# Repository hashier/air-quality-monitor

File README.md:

# air-quality-monitor

DIY air quality monitor on an ESP32-C6, running ESPHome and reporting to Home Assistant.

## Hardware

- **ESP32-C6** dev board (`esp32-c6-devkitc-1`)
- **Sensirion SCD40**: CO2, temperature, humidity (I2C `0x62`)
- **Sensirion SPS30**: particulate matter PM1.0 / 2.5 / 4.0 / 10.0 (I2C `0x69`, 5V)
- **SSD1306** 128x64 OLED (I2C `0x3C`)
- **WS2812** RGB LED (GPIO8)
- **ENS160 + AHT21** combo module: TVOC plus derived eCO2/AQI, AHT21
  temperature/humidity for compensation (I2C `0x52` / `0x38`). Under
  evaluation on the breadboard; mainly calculated values instead of measured
  ones, so it probably won't make the final PCB.

All devices share one I2C bus at 100 kHz (the SPS30 datasheet ceiling).

## Repo layout

- `esphome/`: firmware (ESPHome config + secrets template)
- `kicad/`: custom PCB (planned)
- `case/`: 3D-printed enclosure (planned)

## Firmware

```fish
cd esphome
cp secrets.yaml.example secrets.yaml   # then fill in real values
esphome run air-quality-monitor.yaml
```

`secrets.yaml` holds WiFi / API / OTA credentials and is gitignored. Never commit it.

## Notes

- **SCD40 auto-recovery:** the sensor can get knocked out of periodic measurement (a flaky power connection resets it). A YAML watchdog detects CO2 going stale and re-inits it over raw I2C (stop, then start). Two Home Assistant diagnostics track this: `CO2 Stall Count` and `CO2 Currently Stalled`.
- **Temperature offset** (`6.5C`) is a provisional self-heating correction for the breadboard build. Re-tune in the final enclosure by comparing side by side against a reference.
- **Warm-up filters** drop the SCD40 startup transient (temperature/humidity 5 min, CO2 30 s).

## Status

Work in progress: currently on a breadboard. Custom PCB and enclosure are next.

## To test

- **Separate 3.3V regulator for the SCD40:** power it from 5V through its own LDO (AP2112K-3.3, 1 µF on input and output, EN tied to VIN) instead of the ESP32 board's 3V3 pin. Sensirion's SCD4x datasheet recommends a separate LDO and allows at most 30 mV supply ripple, and the SCD40 peaks at 205 mA while the ESP32's WiFi bursts share the same regulator. Compare `CO2 Stall Count` before and after.
- **Everything on one I2C bus:** SCD40, OLED and SPS30 together, with the SPS30 on a cable as long as the case needs. Each breakout brings its own pull-ups, so check whether the bus still works with all of them in parallel, and whether the SPS30 needs extra ones.

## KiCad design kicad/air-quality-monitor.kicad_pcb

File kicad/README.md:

# kicad

Custom PCB design (KiCad) for the air quality monitor. Planned.

Target layout: thermal zoning so the SCD40 sits away from the ESP32 and
regulator heat and the SPS30 exhaust, on a slot-isolated peninsula, with the
SPS30 airflow ducted to separate case vents. See the project notes for details.

## v1 design (draft, untested)

**Untested.** Nothing below has been built yet. Parts of it depend on the
breadboard tests in the main README's "To test" section, and change if a test
says so.

One PCB for every build, ordered in a batch of 5 and hand-soldered (through-hole
where possible, no assembly service). Each build gets its own 3D-printed case:

| Build | SCD40 | OLED | SPS30 |
|---|---|---|---|
| Living room | yes | yes | yes |
| Bedroom | yes | no | no |
| Portable (power bank, car) | yes | yes | no |

Home Assistant is the control plane, so there are no buttons or buzzers. Unused
dev board pins keep their holes for wiring something on later. Battery power is
for a later version.

### Power

- **Input:** a USB-C breakout board (AliExpress 1005004848153846, 20.2 x 14 mm)
  on an 8-pin 2.54 mm header, 5V, no USB PD. Only VBUS and GND are wired. The
  board has its own 5.1 kΩ resistors on CC1 and CC2, so a USB-C charger turns
  on 5V. Pin order and screw holes still need checking on the real board.
- **5V rail** feeds the SPS30 and both 3.3V regulators directly.
- **Dev board 5V pin** (J1 pin 14) is fed from the 5V rail through a Schottky
  diode, which a jumper cap bypasses by default (see below). With the cap
  pulled, plugging in the dev board's own USB at the same time can't push
  current back into the PCB's USB-C. In Espressif's DevKitC-1 schematic v1.4,
  each USB port reaches `VCC_5V` through a 1N5819, and `VCC_5V` is the 5V pin
  with no diode in between.
- **Two AP2112K-3.3** (SOT-23-5) from the 5V rail, each with EN tied to VIN and
  1 µF on input and output, instead of the dev board's 3V3, which also feeds the
  WiFi:
  - **3V3_SCD** feeds only the SCD40. Pending the LDO test.
  - **3V3_AUX** feeds the OLED and the two JST ZH sensor sockets.
- **Fallback to the dev board's rails:**
  - each 3.3V rail can be switched to the dev board's 3V3 pin with a 3-pad
    solder jumper (`SolderJumper_3_Bridged12`): a thin trace joins the LDO side
    from the factory, so the board works without soldering a jumper; to switch,
    cut it and put a solder blob on the dev board side. Solder jumpers,
    not pin headers with caps, because a push-fit contact in the SCD40's supply
    is the kind of fault behind the earlier stalls;
  - a 2-pin header with a jumper cap (`Jumper_2_Bridged`) across the Schottky
    diode, cap on by default: the dev board gets the full 5V, not 5V minus the
    diode drop, likely too little for its AMS1117 (an ESP32-S3 board went into
    a brownout loop at 4.9V on its 5V pin). A loose cap only puts the diode back
    in the path. Pull the cap before plugging in both USB cables, otherwise the
    device on the PCB's USB-C gets fed backwards. With the cap on, the dev board's
    own USB also powers the whole PCB;
  - two optional electrolytics (C6 100µF, C7 470µF, not fitted) on the dev
    board's 3V3 pin: that pair (570µF) stopped the same S3 board's brownout loop
    at 5.0V.

### Dev board

ESP32-C6-DevKitC-1 or a pin-compatible copy, soldered through its pin headers:
2 rows of 16 pins at 2.54 mm, rows 22.86 mm apart, board 25.4 × 51.8 mm
(Espressif dimension drawing v1.2). Pin 16 on both rows stays unconnected:
it is NC on Espressif's board and GND on the QSZNTEC copy.

Every header hole the PCB connects to (5V, 3V3, SDA, SCL, and GND on two pins
with one jumper each) goes through a cuttable solder jumper
(`SolderJumper_2_Bridged` in KiCad's `Jumper` library), so another board's pin
in that position is never shorted to anything. A board with a
different pinout fits by cutting the jumper and wiring its pin to the jumper's
pad. This does not fix a different row distance.

I2C stays on the pins the firmware uses today: SDA GPIO21, SCL GPIO22, at
100 kHz (the SPS30 maximum).

### Sensors and display

- **SCD40:** the breakout (pins SDA, SCL, VDD, GND; it already has its own
  pull-ups R1/R2 and C1), soldered on permanently through its pin header. Far
  from the dev board, both AP2112Ks and the SPS30 exhaust.
- **OLED:** 4 holes at the board edge in the module's order GND, VDD, SCK, SDA.
  Solder the module straight in, run wires to place it elsewhere in a case, or
  leave it out. No copper or parts under the module.
- **SPS30 (optional):** JST ZH 5-pin socket (B5B-ZR) for its ZHR-5 cable. Pins
  per the SPS30 datasheet v2.0: 1 VDD (5V, 4.5 to 5.5V), 2 SDA, 3 SCL, 4 SEL,
  5 GND. SEL goes to GND to select I2C. Up to 80 mA during fan start. Sensirion
  recommends UART over I2C for cables longer than 20 cm.
- **Sensor sockets (1 or 2):** for trying out other I2C sensors (the ENS160 and
  AHT21 module, for example), each soldered to a ZH cable. JST ZH 4-pin,
  1.5 mm pitch, through-hole (B4B-ZR), pin order GND, 3.3V, SDA, SCL as in
  SparkFun's Qwiic. Not Qwiic plugs: Qwiic uses the smaller surface-mount
  JST SH (1 mm pitch), too fine to solder by hand here.

### Still open

- Pull-ups: the SCD40 breakout and probably the OLED module bring their own,
  and the SPS30 needs some on the bus. Whether the PCB adds pull-ups is
  decided by the bus test.
- Exact Schottky diode and capacitor parts, picked with the footprints.
  C1 to C5 have 4 holes, for leads 2.5 mm or 5 mm apart, until the
  capacitors at hand are measured. C1 (10 µF) has an electrolytic footprint
  with a + mark, which also takes a ceramic one.
- ESP32-S3 dev board (2 × 22 pins from a photo, rows 25.4 mm apart: measured
  about 25 mm with a folding ruler) is not supported in v1.

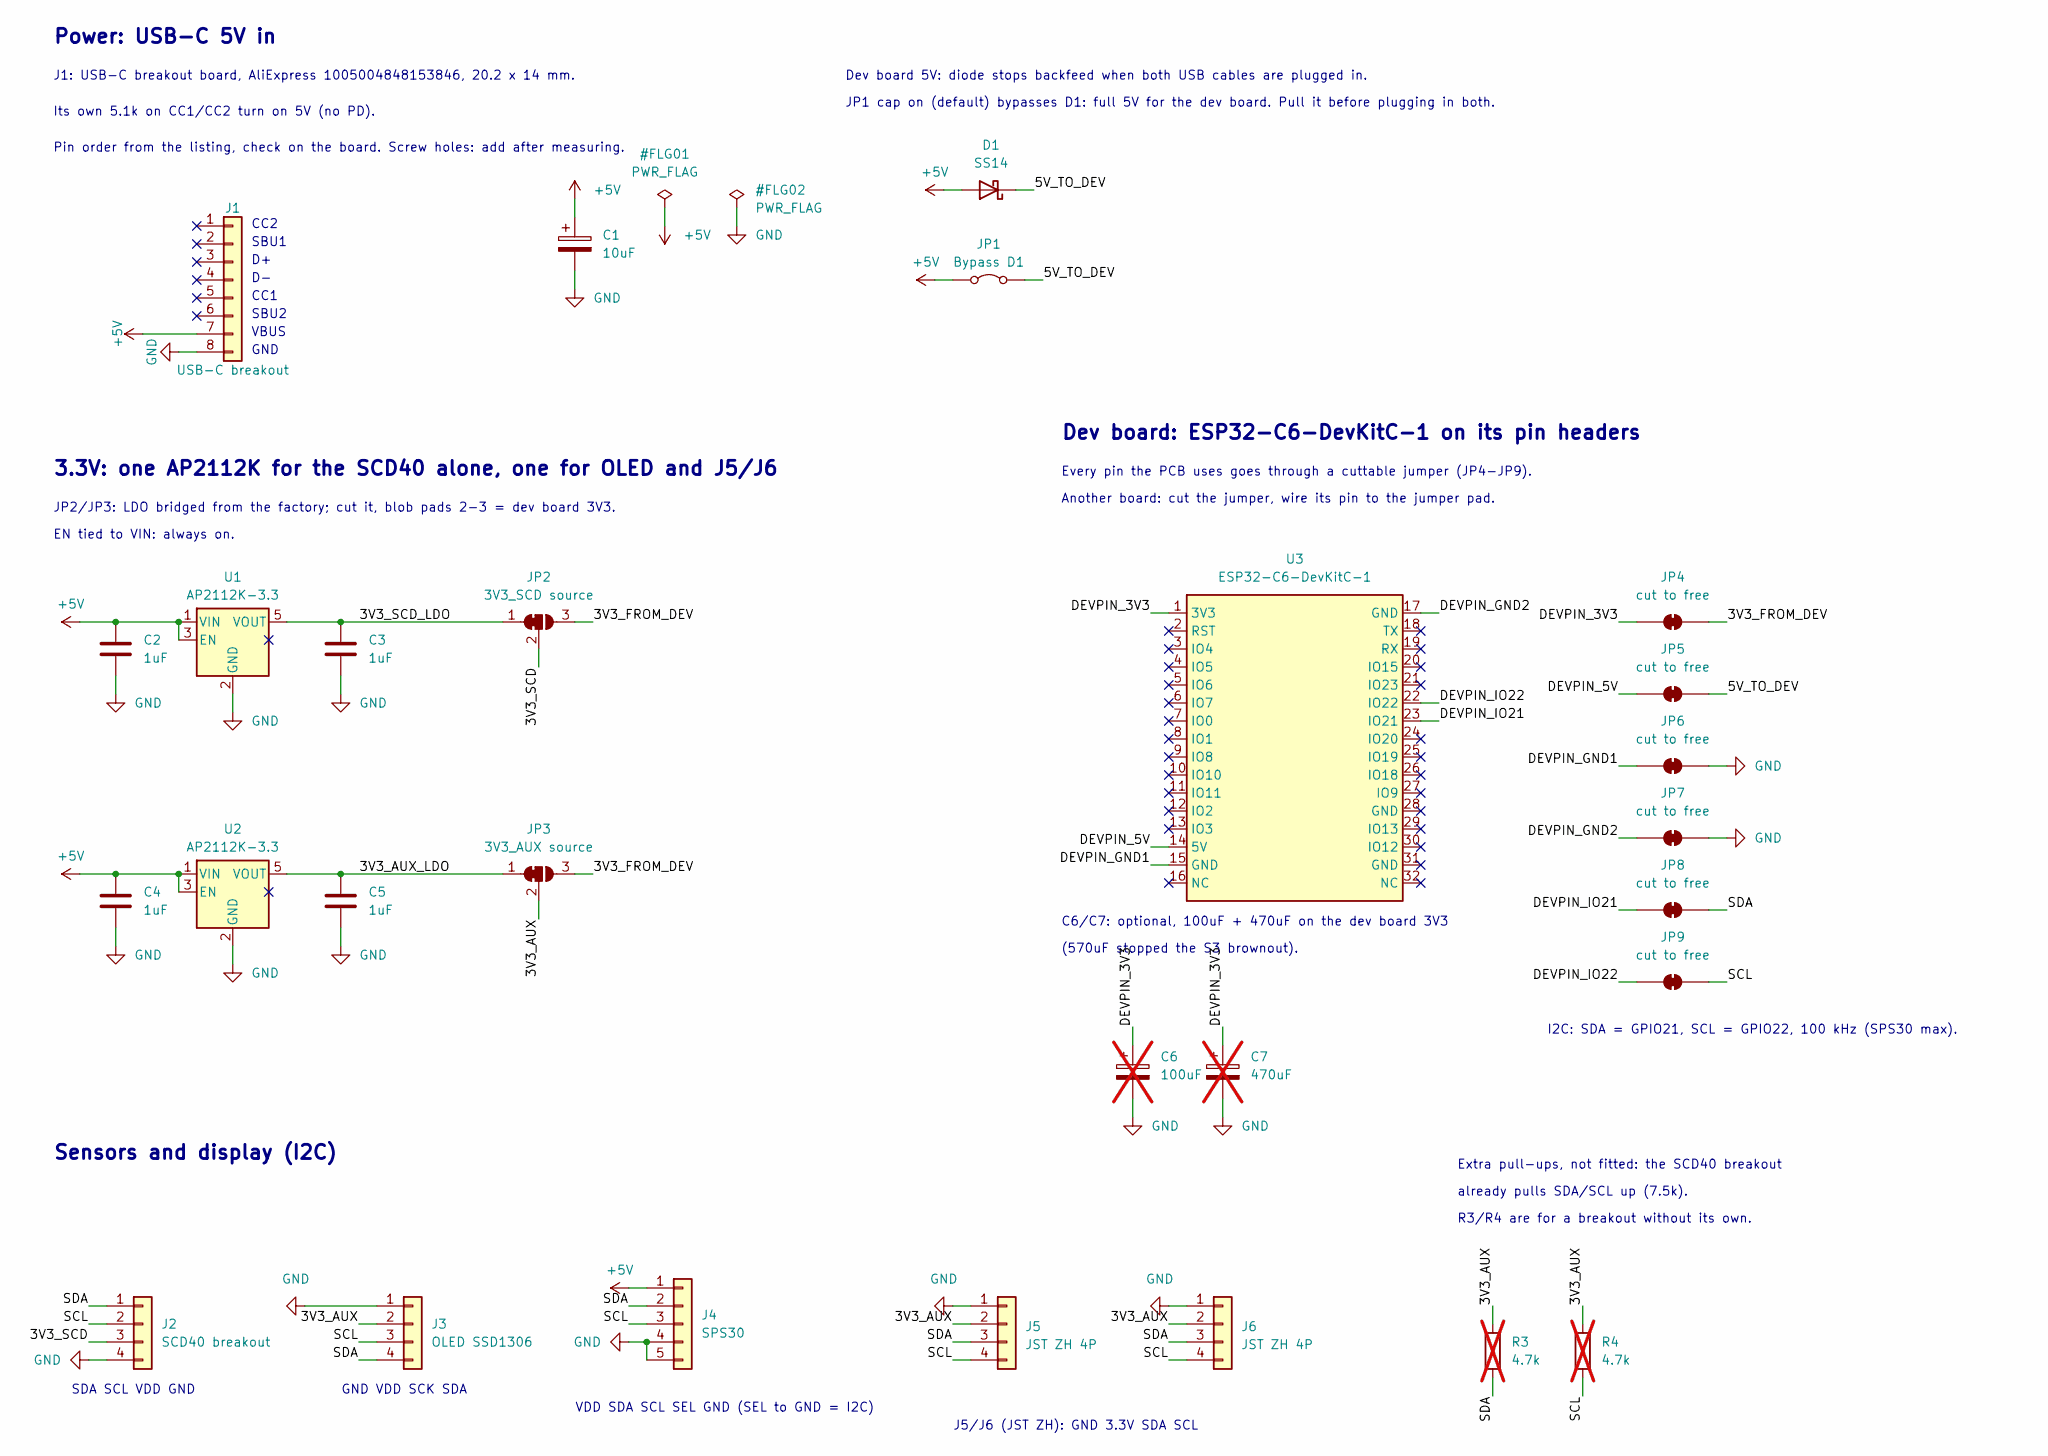
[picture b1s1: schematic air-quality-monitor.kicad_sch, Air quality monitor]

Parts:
C1: 10uF; CP_Radial_D10.0mm_P2.50mm_P5.00mm
C2, C3, C4, C5: 1uF; C_Rect_L7.0mm_W3.5mm_P2.50mm_P5.00mm
C6: 100uF; CP_Radial_D8.0mm_P2.50mm; not fitted
C7: 470uF; CP_Radial_D8.0mm_P2.50mm; not fitted
D1: SS14; D_SMA
J1: USB-C breakout; PinHeader_1x08_P2.54mm_Vertical
J2: SCD40 breakout; PinHeader_1x04_P2.54mm_Vertical
J3: OLED SSD1306; PinHeader_1x04_P2.54mm_Vertical
J4: SPS30; JST_ZH_B5B-ZR_1x05_P1.50mm_Vertical
J5, J6: JST ZH 4P; JST_ZH_B4B-ZR_1x04_P1.50mm_Vertical
JP1: Bypass D1; PinHeader_1x02_P2.54mm_Vertical
JP2: 3V3_SCD source; SolderJumper-3_P1.3mm_Bridged12_RoundedPad1.0x1.5mm_NumberL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
JP3: 3V3_AUX source; SolderJumper-3_P1.3mm_Bridged12_RoundedPad1.0x1.5mm_NumberL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
JP4, JP5, JP6, JP7, JP8, JP9: cut to free; SolderJumper-2_P1.3mm_Bridged_RoundedPad1.0x1.5mm
R3, R4: 4.7k; R_Axial_DIN0207_L6.3mm_D2.5mm_P10.16mm_Horizontal; not fitted
U1, U2: AP2112K-3.3; SOT-23-5_HandSoldering
U3: ESP32-C6-DevKitC-1

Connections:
+5V: C1.1, C2.1, C4.1, D1.2 (A), J1.7, J4.1, JP1.1 (A), U1.1 (VIN), U1.3 (EN), U2.1 (VIN), U2.3 (EN)
/3V3_AUX: J3.2, J5.2, J6.2, JP3.2 (C), R3.1, R4.1
/3V3_AUX_LDO: C5.1, JP3.1 (A), U2.5 (VOUT)
/3V3_FROM_DEV: JP2.3 (B), JP3.3 (B), JP4.2 (B)
/3V3_SCD: J2.3, JP2.2 (C)
/3V3_SCD_LDO: C3.1, JP2.1 (A), U1.5 (VOUT)
/5V_TO_DEV: D1.1 (K), JP1.2 (B), JP5.2 (B)
/DEVPIN_3V3: C6.1, C7.1, JP4.1 (A), U3.1 (3V3)
/DEVPIN_5V: JP5.1 (A), U3.14 (5V)
/DEVPIN_GND1: JP6.1 (A), U3.15 (GND)
/DEVPIN_GND2: JP7.1 (A), U3.17 (GND)
/DEVPIN_IO21: JP8.1 (A), U3.23 (IO21)
/DEVPIN_IO22: JP9.1 (A), U3.22 (IO22)
/SCL: J2.2, J3.3, J4.3, J5.4, J6.4, JP9.2 (B), R4.2
/SDA: J2.1, J3.4, J4.2, J5.3, J6.3, JP8.2 (B), R3.2
GND: C1.2, C2.2, C3.2, C4.2, C5.2, C6.2, C7.2, J1.8, J2.4, J3.1, J4.4, J4.5, J5.1, J6.1, JP6.2 (B), JP7.2 (B), U1.2 (GND), U2.2 (GND)

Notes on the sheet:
Another board: cut the jumper, wire its pin to the jumper pad.
3.3V: one AP2112K for the SCD40 alone, one for OLED and J5/J6
Every pin the PCB uses goes through a cuttable jumper (JP4-JP9).
EN tied to VIN: always on.
JP1 cap on (default) bypasses D1: full 5V for the dev board. Pull it before plugging in both.
Dev board 5V: diode stops backfeed when both USB cables are plugged in.
SDA SCL VDD GND
Dev board: ESP32-C6-DevKitC-1 on its pin headers
J5/J6 (JST ZH): GND 3.3V SDA SCL
Power: USB-C 5V in
GND VDD SCK SDA
Extra pull-ups, not fitted: the SCD40 breakout
already pulls SDA/SCL up (7.5k).
R3/R4 are for a breakout without its own.
Sensors and display (I2C)
C6/C7: optional, 100uF + 470uF on the dev board 3V3
JP2/JP3: LDO bridged from the factory; cut it, blob pads 2-3 = dev board 3V3.
VDD SDA SCL SEL GND (SEL to GND = I2C)
I2C: SDA = GPIO21, SCL = GPIO22, 100 kHz (SPS30 max).
(570uF stopped the S3 brownout).
J1: USB-C breakout board, AliExpress 1005004848153846, 20.2 x 14 mm.
Its own 5.1k on CC1/CC2 turn on 5V (no PD).
Pin order from the listing, check on the board. Screw holes: add after measuring.
CC2
SBU1
CC1
SBU2
VBUS
GND

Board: 2 copper layers, 28 parts (0 on the bottom side), 16 nets, no tracks yet.

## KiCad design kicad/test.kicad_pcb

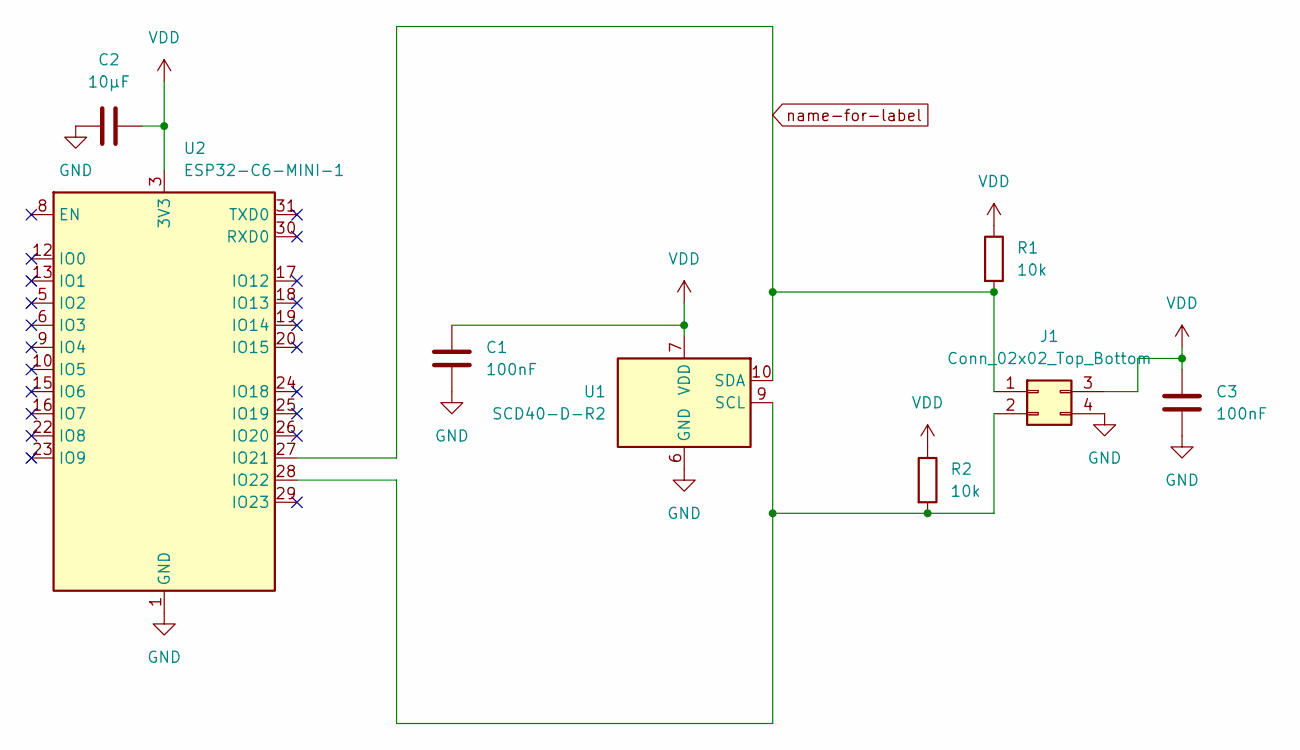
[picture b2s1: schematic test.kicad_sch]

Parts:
C1, C3: 100nF; C_0603_1608Metric_Pad1.08x0.95mm_HandSolder
C2: 10µF; C_0603_1608Metric_Pad1.08x0.95mm_HandSolder
J1: Conn_02x02_Top_Bottom; PinHeader_2x02_P2.54mm_Vertical
R1, R2: 10k; R_0603_1608Metric_Pad0.98x0.95mm_HandSolder
U1: SCD40-D-R2; Sensirion_SCD4x-1EP_10.1x10.1mm_P1.25mm_EP4.8x4.8mm
U2: ESP32-C6-MINI-1

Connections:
GND: C1.2, C2.2, C3.2, J1.4, U1.6 (GND), U1.20 (GND), U1.21 (GND), U2.1 (GND), U2.2 (GND), U2.11 (GND), U2.14 (GND), U2.36 (GND), U2.37 (GND), U2.38 (GND), U2.39 (GND), U2.40 (GND), U2.41 (GND), U2.42 (GND), U2.43 (GND), U2.44 (GND), U2.45 (GND), U2.46 (GND), U2.47 (GND), U2.48 (GND), U2.49 (GND), U2.50 (GND), U2.51 (GND), U2.52 (GND), U2.53 (GND)
unnamed: J1.2, R2.2, U1.9 (SCL), U2.28 (IO22)
VDD: C1.1, C2.1, C3.1, J1.3, R1.1, R2.1, U1.7 (VDD), U1.19 (VDD), U2.3 (3V3)
name-for-label: J1.1, R1.2, U1.10 (SDA), U2.27 (IO21)

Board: 2 copper layers, 8 parts (0 on the bottom side), 4 nets, no tracks yet.
